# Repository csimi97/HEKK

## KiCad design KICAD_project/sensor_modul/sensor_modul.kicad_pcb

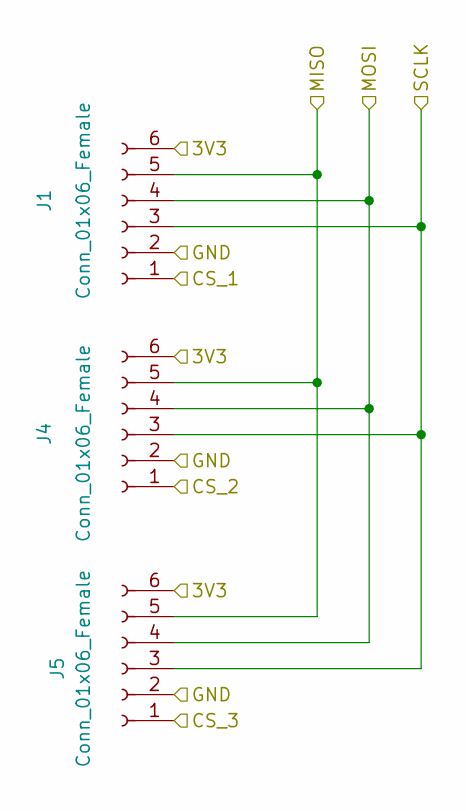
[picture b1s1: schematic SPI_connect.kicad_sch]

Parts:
J1, J4, J5: Conn_01x06_Female; PinHeader_1x06_P2.54mm_Vertical

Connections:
+3V3: J1.6, J4.6, J5.6; also elsewhere on the board
/EFR32/SPI_CLK: J1.3, J4.3, J5.3; also elsewhere on the board
/EFR32/SPI_CS1: J1.1; also elsewhere on the board
/EFR32/SPI_CS2: J4.1; also elsewhere on the board
/EFR32/SPI_CS3: J5.1; also elsewhere on the board
/EFR32/SPI_MISO: J1.5, J4.5, J5.5; also elsewhere on the board
/EFR32/SPI_MOSI: J1.4, J4.4, J5.4; also elsewhere on the board
GND: J1.2, J4.2, J5.2; also elsewhere on the board

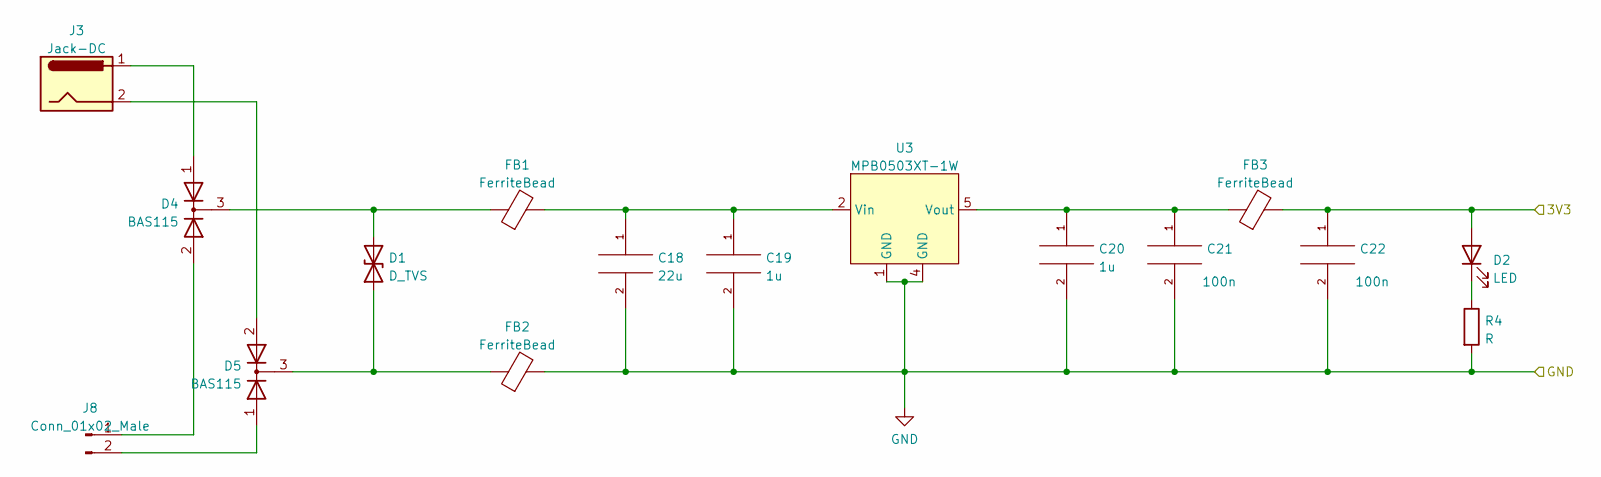
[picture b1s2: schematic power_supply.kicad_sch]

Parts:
C18: 22u; C_0805_2012Metric
C19, C20: 1u; C_0805_2012Metric
C21, C22: 100n; C_0805_2012Metric
D1: D_TVS; D_SMB
D2: LED; C_0805_2012Metric
D4, D5: BAS115; SOT-23
FB1, FB2, FB3: FerriteBead; L_0805_2012Metric
J3: Jack-DC; BarrelJack_CLIFF_FC681465S_SMT_Horizontal
J8: Conn_01x02_Male; PinHeader_1x02_P2.54mm_Vertical
R4: R; C_0805_2012Metric
U3: MPB0503XT-1W

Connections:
+3V3: C22.1, D2.2 (A), FB3.2; also elsewhere on the board
GND: C18.2, C19.2, C20.2, C21.2, C22.2, FB2.2, R4.2, U3.1 (GND), U3.4 (GND); also elsewhere on the board
unnamed: C18.1, C19.1, FB1.2, U3.2 (Vin)
unnamed: C20.1, C21.1, FB3.1, U3.5 (Vout)
unnamed: D1.1 (A1), D5.3 (K), FB2.1
unnamed: D1.2 (A2), D4.3 (K), FB1.1
unnamed: D2.1 (K), R4.1
unnamed: D4.1 (A), J3.1
unnamed: D4.2 (A), J8.1
unnamed: D5.1 (A), J8.2
unnamed: D5.2 (A), J3.2

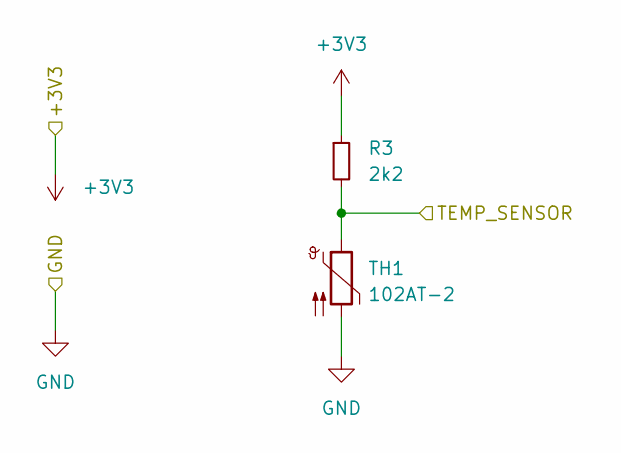
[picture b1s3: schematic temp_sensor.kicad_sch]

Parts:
R3: 2k2; R_0805_2012Metric
TH1: 102AT-2; PinHeader_1x02_P2.54mm_Vertical

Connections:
+3V3: R3.1; also elsewhere on the board
/EFR32/Temp_sense: R3.2, TH1.1; also elsewhere on the board
GND: TH1.2; also elsewhere on the board

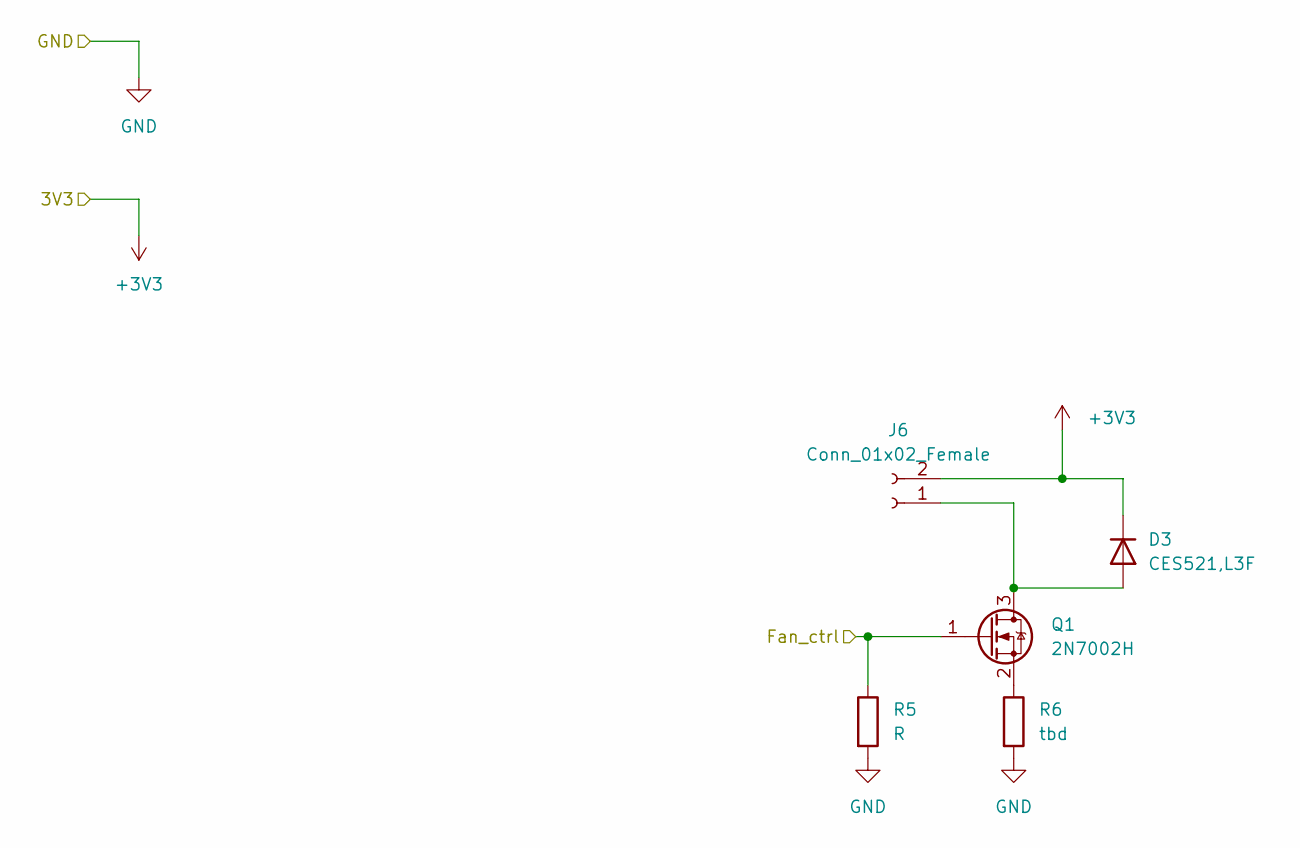
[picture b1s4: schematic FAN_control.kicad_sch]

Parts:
D3: CES521,L3F; D_SOD-523
J6: Conn_01x02_Female; PinHeader_1x02_P2.54mm_Vertical
Q1: 2N7002H; SOT-23
R5: R; R_0805_2012Metric
R6: tbd; R_0805_2012Metric

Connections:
+3V3: D3.1 (K), J6.2; also elsewhere on the board
/EFR32/FAN_ctrl: Q1.1 (G), R5.1; also elsewhere on the board
GND: R5.2, R6.2; also elsewhere on the board
unnamed: D3.2 (A), J6.1, Q1.3 (D)
unnamed: Q1.2 (S), R6.1

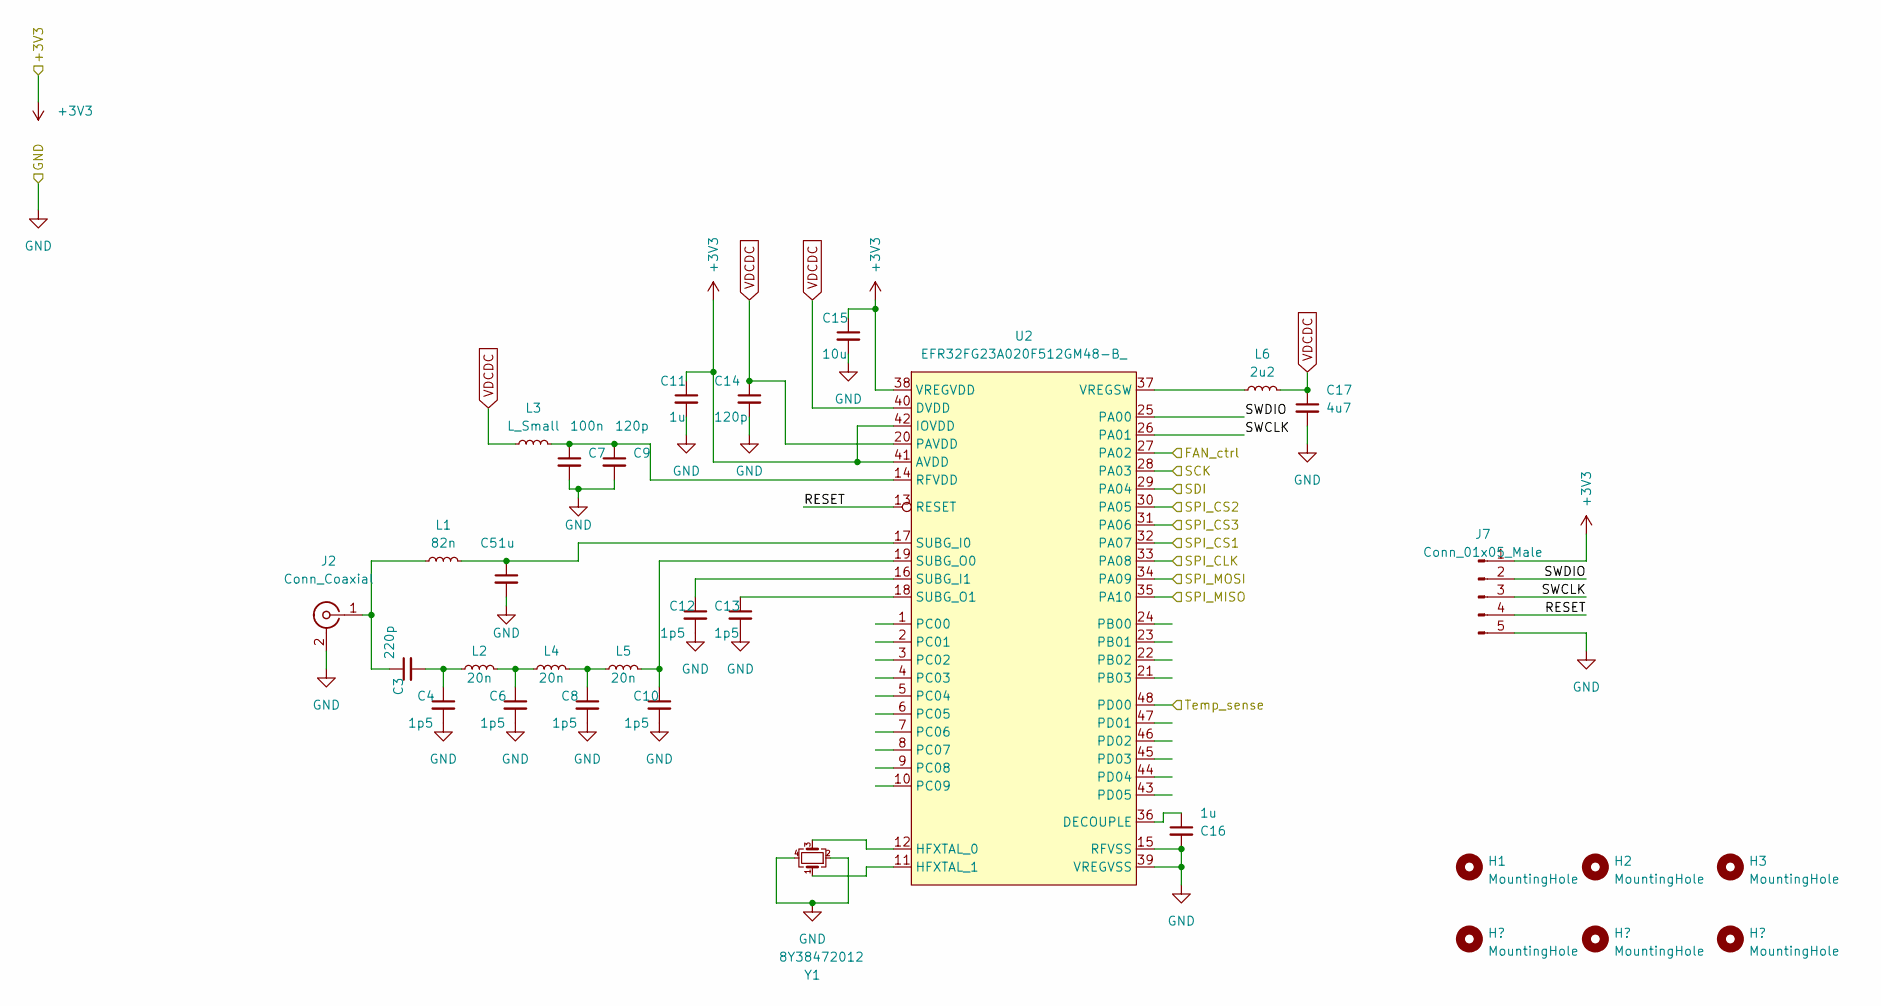
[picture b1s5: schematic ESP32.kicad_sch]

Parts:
C3: 220p; R_0402_1005Metric
C4, C6, C8, C10, C12, C13: 1p5; R_0402_1005Metric
C5: 1u; R_0402_1005Metric
C7: 100n; R_0402_1005Metric
C9, C14: 120p; R_0402_1005Metric
C11, C16: 1u; R_0805_2012Metric
C15: 10u; R_1206_3216Metric
C17: 4u7; R_0805_2012Metric
H1, H2, H3: MountingHole; MountingHole_2.2mm_M2
J2: Conn_Coaxial; SMA_Samtec_SMA-J-P-X-ST-EM1_EdgeMount
J7: Conn_01x05_Male; PinHeader_1x05_P2.54mm_Vertical
L1: 82n; R_0402_1005Metric
L2, L4, L5: 20n; R_0402_1005Metric
L3: L_Small; R_0402_1005Metric
L6: 2u2; R_0402_1005Metric
U2: EFR32FG23A020F512GM48-B_; EFR32FG23A020F512GM48-B
Y1: 8Y38472012; Oscillator_SMD_SeikoEpson_SG210-4Pin_2.5x2.0mm

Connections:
+3V3: C11.1, C15.1, J7.1, U2.38 (VREGVDD), U2.41 (AVDD), U2.42 (IOVDD); also elsewhere on the board
/Air_Quality_sensor/AQ_SENSOR_SCL: U2.28 (PA03); also elsewhere on the board
/Air_Quality_sensor/AQ_SENSOR_SDA: U2.29 (PA04); also elsewhere on the board
/EFR32/FAN_ctrl: U2.27 (PA02); also elsewhere on the board
/EFR32/RESET: J7.4, U2.13 (RESET)
/EFR32/SPI_CLK: U2.33 (PA08); also elsewhere on the board
/EFR32/SPI_CS1: U2.32 (PA07); also elsewhere on the board
/EFR32/SPI_CS2: U2.30 (PA05); also elsewhere on the board
/EFR32/SPI_CS3: U2.31 (PA06); also elsewhere on the board
/EFR32/SPI_MISO: U2.35 (PA10); also elsewhere on the board
/EFR32/SPI_MOSI: U2.34 (PA09); also elsewhere on the board
/EFR32/SWCLK: J7.3, U2.26 (PA01)
/EFR32/SWDIO: J7.2, U2.25 (PA00)
/EFR32/Temp_sense: U2.48 (PD00); also elsewhere on the board
GND: C4.2, C5.2, C6.2, C7.2, C8.2, C9.2, C10.2, C11.2, C12.2, C13.2, C14.2, C15.2, C16.2, C17.2, J2.2 (Ext), J7.5, U2.15 (RFVSS), U2.39 (VREGVSS), Y1.2, Y1.4; also elsewhere on the board
unnamed: C3.1, J2.1 (In), L1.1
unnamed: C3.2, C4.1, L2.1
unnamed: C5.1, L1.2, U2.17 (SUBG_I0)
unnamed: C6.1, L2.2, L4.1
unnamed: C7.1, C9.1, L3.2, U2.14 (RFVDD)
unnamed: C8.1, L4.2, L5.1
unnamed: C10.1, L5.2, U2.19 (SUBG_O0)
unnamed: C12.1, U2.16 (SUBG_I1)
unnamed: C13.1, U2.18 (SUBG_O1)
unnamed: C16.1, U2.36 (DECOUPLE)
unnamed: L6.1, U2.37 (VREGSW)
unnamed: U2.11 (HFXTAL_1), Y1.1
unnamed: U2.12 (HFXTAL_0), Y1.3
VDCDC: C14.1, C17.1, L3.1, L6.2, U2.20 (PAVDD), U2.40 (DVDD)

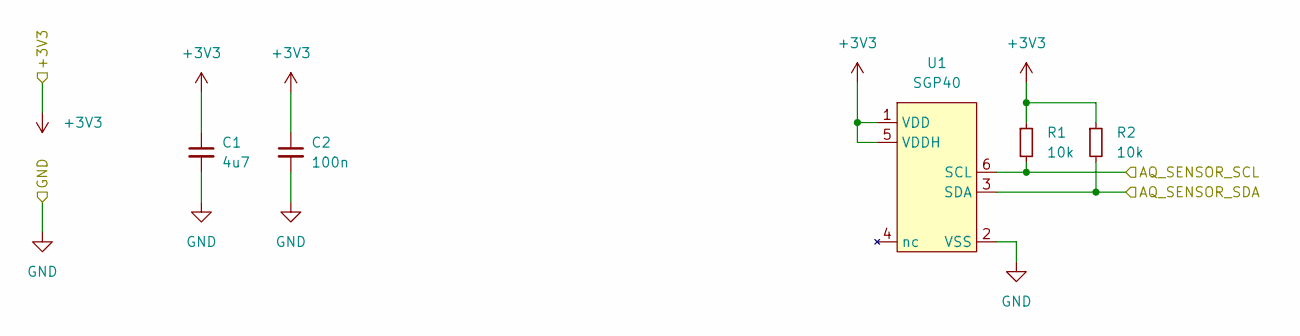
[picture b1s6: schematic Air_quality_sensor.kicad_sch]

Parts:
C1: 4u7; R_0805_2012Metric
C2: 100n; R_0805_2012Metric
R1, R2: 10k; R_0805_2012Metric
U1: SGP40

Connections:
+3V3: C1.1, C2.1, R1.1, R2.1, U1.1 (VDD), U1.5 (VDDH); also elsewhere on the board
/Air_Quality_sensor/AQ_SENSOR_SCL: R1.2, U1.6 (SCL); also elsewhere on the board
/Air_Quality_sensor/AQ_SENSOR_SDA: R2.2, U1.3 (SDA); also elsewhere on the board
GND: C1.2, C2.2, U1.2 (VSS), U1.7; also elsewhere on the board

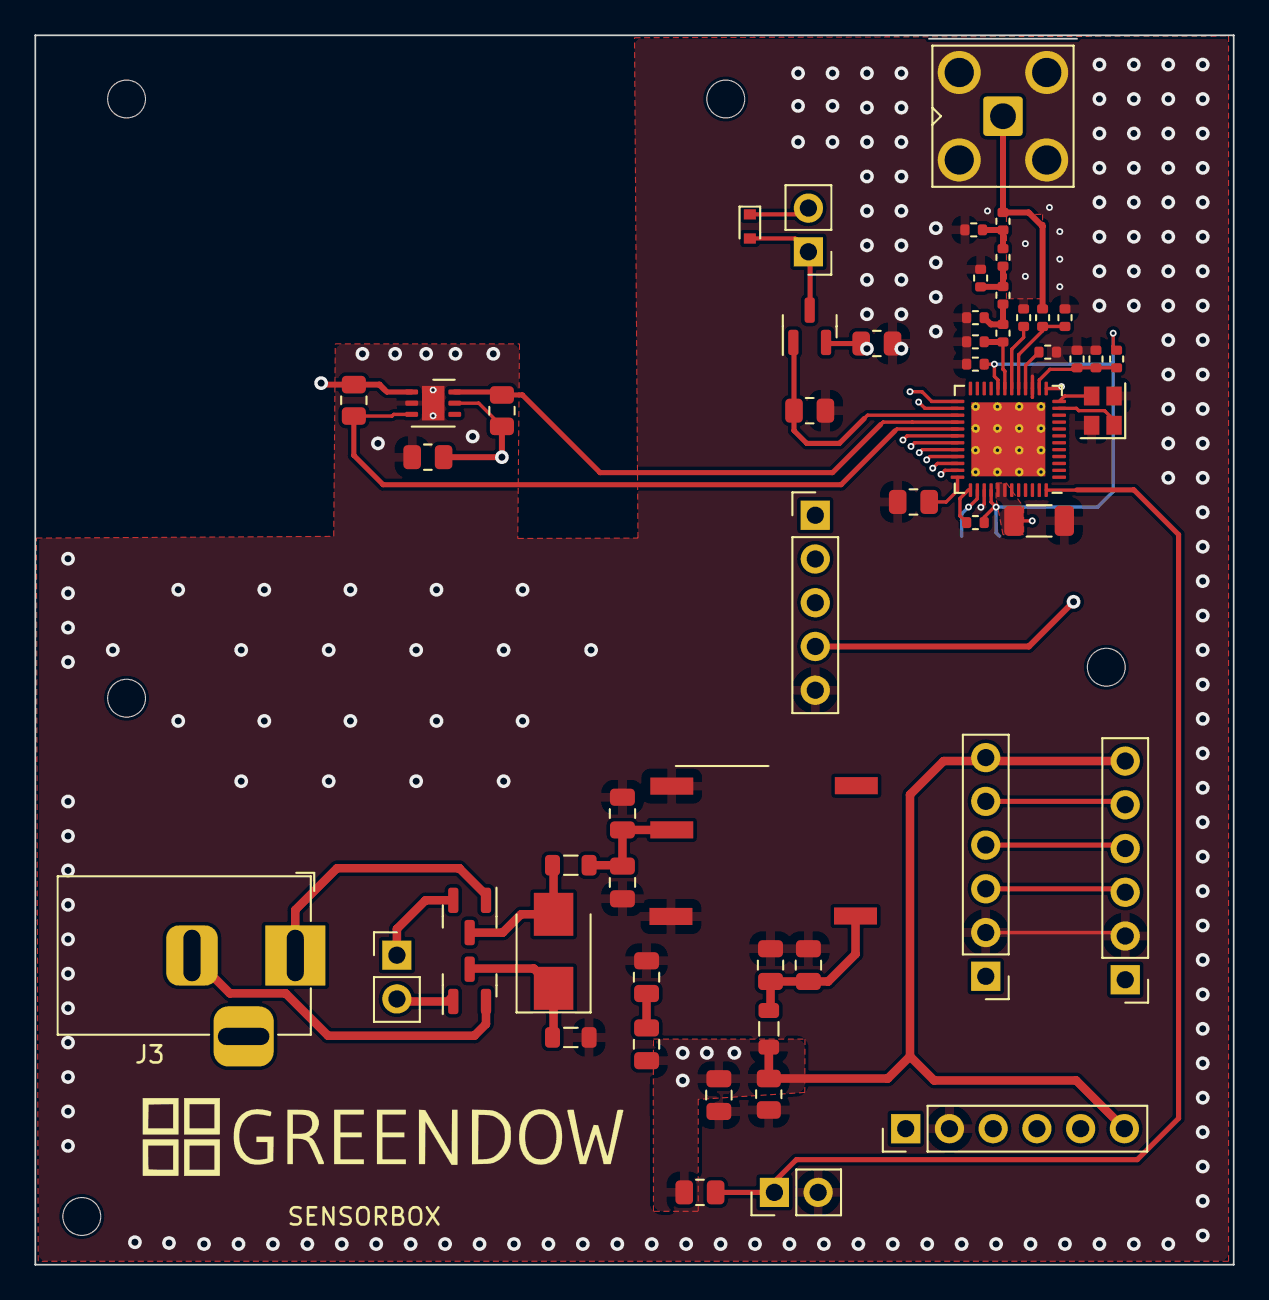
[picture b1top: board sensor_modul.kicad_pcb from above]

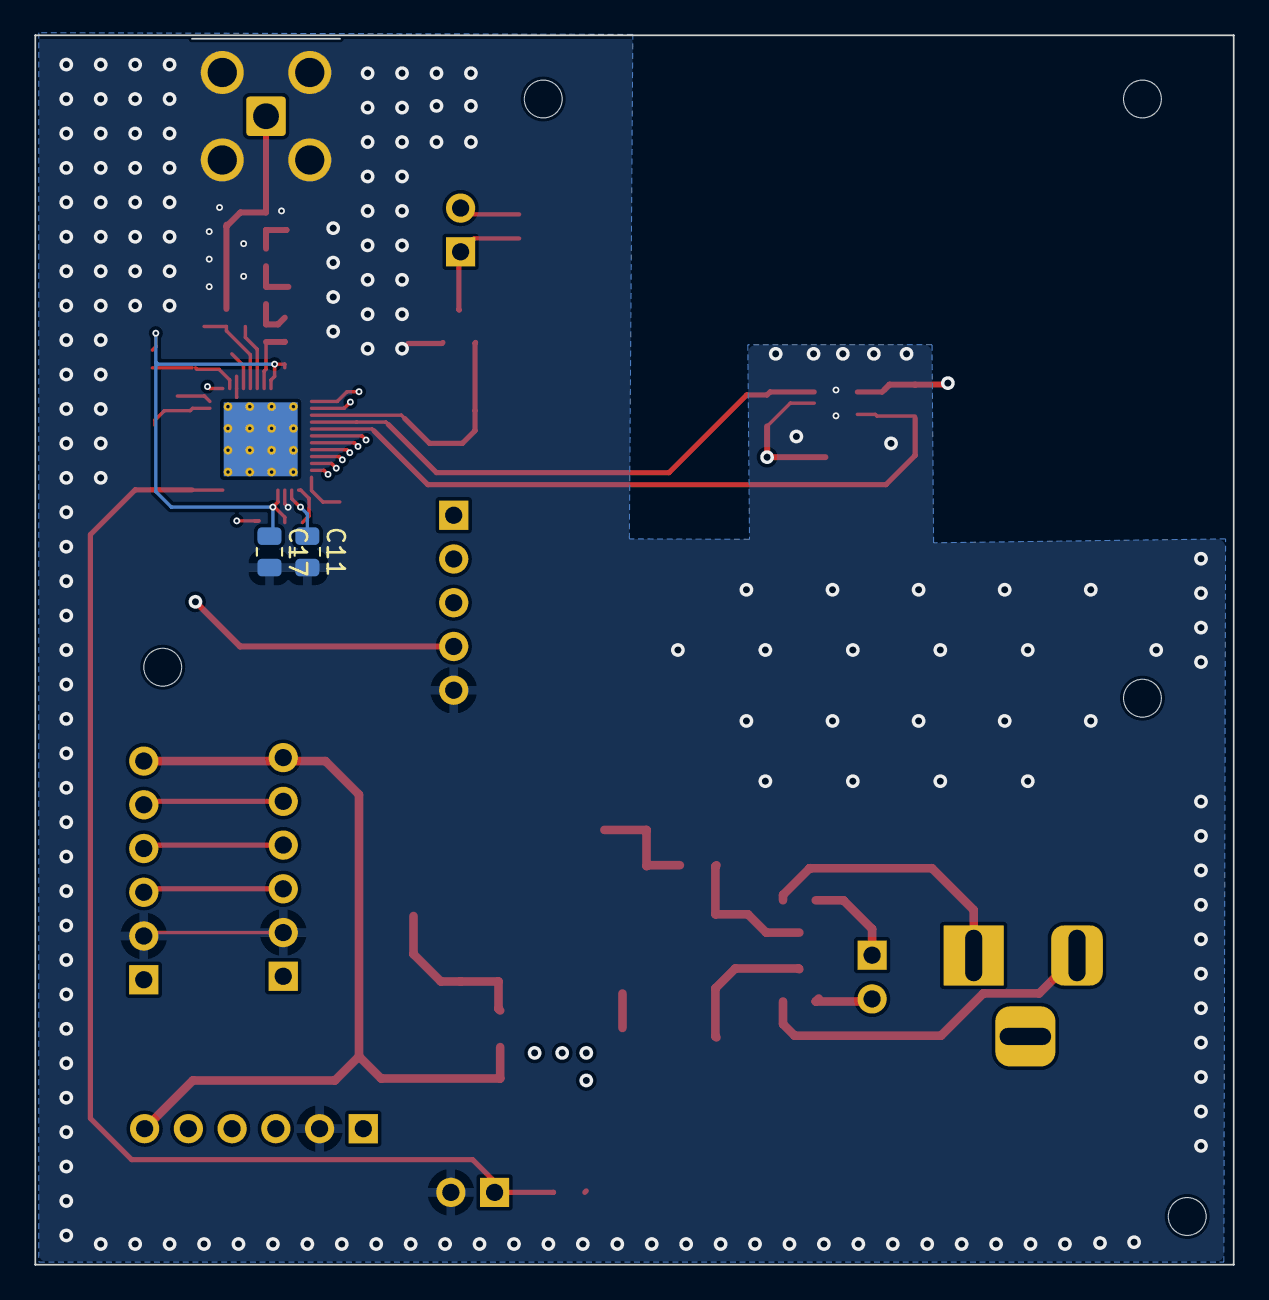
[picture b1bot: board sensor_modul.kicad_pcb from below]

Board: 4 copper layers, 69.6 x 71.4 mm, 61 parts (2 on the bottom side), 40 nets.

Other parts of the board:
H4, H6: MountingHole; MountingHole_2.2mm_M2

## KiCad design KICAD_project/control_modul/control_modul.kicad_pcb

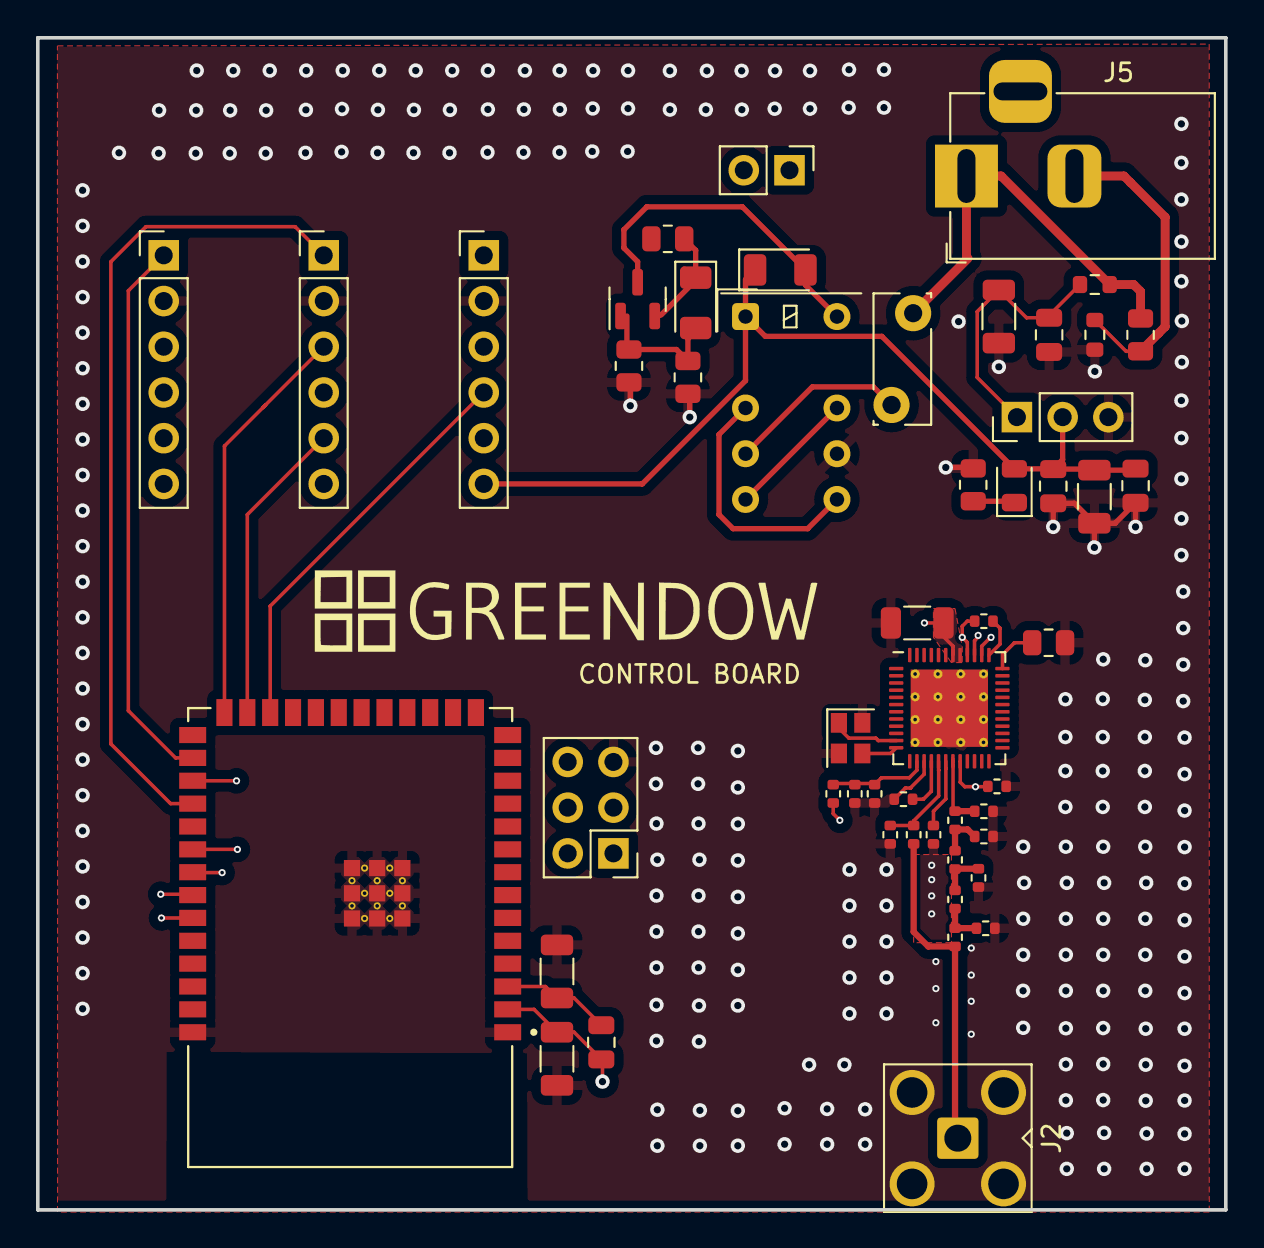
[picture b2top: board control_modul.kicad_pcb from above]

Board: 4 copper layers, 66.0 x 65.1 mm, 51 parts (0 on the bottom side), 37 nets.

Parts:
C1, C22: 22u; C_1206_3216Metric
C3: 220p; R_0402_1005Metric
C4, C6, C8, C10, C12, C13: 1p5; R_0402_1005Metric
C5: 1u; R_0402_1005Metric
C7: 100n; R_0402_1005Metric
C9, C14: 120p; R_0402_1005Metric
C15: 10u; R_1206_3216Metric
C16: 1u; R_0805_2012Metric
C18: 100n; C_1206_3216Metric
C19, C23: 1u; C_0805_2012Metric
C20: 33u; R_0805_2012Metric
C21: 10u; C_1206_3216Metric
C24: 100n; C_0805_2012Metric
D1, D2: 1N4148; D_1206_3216Metric
D3: D_TVS; R_0805_2012Metric
D4: LED; LED_0805_2012Metric
F1: Fuse; Fuse_Bourns_MF-RG300
FB2, FB3: FerriteBead; R_0603_1608Metric
J1, J3, J4: Conn_01x06_Female; PinHeader_1x06_P2.54mm_Vertical
J2: Conn_Coaxial; SMA_Amphenol_901-143_Horizontal
J5: Jack-DC; BarrelJack_Horizontal
J6: Conn_01x02_Female; PinHeader_1x02_P2.54mm_Vertical
J7: Conn_01x06_Female; PinHeader_2x03_P2.54mm_Vertical
K1: EC2-3NU; Relay_DPDT_Kemet_EC2
L1: 82n; R_0402_1005Metric
L2, L4, L5: 20n; R_0402_1005Metric
L3: L_Small; R_0402_1005Metric
L6: 2u2; R_0402_1005Metric
Q1: PN2222A; SOT-23
R1: 47k; R_0805_2012Metric
R2: 820k; R_0805_2012Metric
R3: 10k; C_0805_2012Metric
R4: R; R_0805_2012Metric
U1: ESP32; XCVR_ESP32-S3-WROOM-1-N16R2
U2: EFR32FG23A020F512GM48-B_; EFR32FG23A020F512GM48-B
U3: P78E05_1000; PinHeader_1x03_P2.54mm_Vertical
Y1: 8Y38472012; Oscillator_SMD_SeikoEpson_SG210-4Pin_2.5x2.0mm

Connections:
+3V3: C1.1, C15.1, C22.1, C23.1, C24.1, D2.1 (K), D4.2 (A), J1.6, J3.6, J4.6, J7.6, K1.1, R3.1, U1.2 (3V3), U2.38 (VREGVDD), U2.41 (AVDD), U2.42 (IOVDD), U3.2 (Vout)
+24V: D3.2 (A2), F1.1, FB3.1, J5.1
/ESP32/CS1: J1.1, U1.28 (IO35)
/ESP32/CS2: J3.1, U1.29 (IO36)
/ESP32/CS3: J4.1, U1.30 (IO37)
/ESP32/MISO: J1.5, J3.5, J4.5, U1.25 (IO48)
/ESP32/MOSI: J1.4, J3.4, J4.4, U1.24 (IO47)
/ESP32/SCLK: J1.3, J3.3, J4.3, U1.26 (IO45)
/ESP32/TCK: J7.2, U1.32 (IO39)
/ESP32/TDI: J7.4, U1.34 (IO41)
/ESP32/TDO: J7.3, U1.33 (IO40)
/ESP32/TMS: J7.1, U1.35 (IO42)
GND: C1.2, C4.2, C5.2, C6.2, C7.2, C8.2, C9.2, C10.2, C12.2, C13.2, C14.2, C15.2, C16.2, C18.1, C19.2, C20.2, C21.2, C22.2, C23.2, C24.2, FB2.2, J1.2, J2.2 (Ext), J3.2, J4.2, J7.5, K1.9, R2.1, R4.2, U1.1 (GND), U1.40 (GND), U1.41_1, U1.41_2, U1.41_3, U1.41_4, U1.41_5, U1.41_6, U1.41_7, U1.41_8, U1.41_9, U1.41_10, U1.41_11, U1.41_12, U1.41_13, U1.41_14, U1.41_15, U1.41_16, U1.41_17, U1.41_18, U1.41_19, U1.41_20, U1.41_21, U2.15 (RFVSS), U2.39 (VREGVSS), U2.49, U3.3 (GND), Y1.2, Y1.4
unnamed: C3.1, J2.1 (In), L1.1
unnamed: C3.2, C4.1, L2.1
unnamed: C5.1, L1.2, U2.17 (SUBG_I0)
unnamed: C6.1, L2.2, L4.1
unnamed: C7.1, C9.1, L3.2, U2.14 (RFVDD)
unnamed: C8.1, L4.2, L5.1
unnamed: C10.1, L5.2, U2.19 (SUBG_O0)
unnamed: C12.1, U2.16 (SUBG_I1)
unnamed: C13.1, U2.18 (SUBG_O1)
unnamed: C16.1, U2.36 (DECOUPLE)
unnamed: C18.2, R3.2, U1.3 (EN)
unnamed: C19.1, C21.1, FB3.2, U3.1 (Vin)
unnamed: C20.1, D1.2 (A), Q1.1 (E), R2.2
unnamed: D1.1 (K), Q1.2 (B), R1.2
unnamed: D2.2 (A), K1.12, Q1.3 (C)
unnamed: D3.1 (A1), FB2.1, J5.2
unnamed: D4.1 (K), R4.1
unnamed: F1.2, K1.4
unnamed: J6.2, K1.3, K1.8
unnamed: J6.1, K1.5, K1.10
unnamed: L6.1, U2.37 (VREGSW)
unnamed: U2.11 (HFXTAL_1), Y1.1
unnamed: U2.12 (HFXTAL_0), Y1.3
VDCDC: C14.1, L3.1, L6.2, U2.20 (PAVDD), U2.40 (DVDD)

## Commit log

2022-09-30 Create TESZT
2022-09-30 teszt
    as
2022-09-30 sdsdsdsdsds
2022-09-30 Boards_schematic_architecture
2022-10-01 control_board_ESP32_symbol_and_footprint
2022-10-01 Added EFR32 Sch and layout
    Added EFR32 Sch and layout
2022-10-01 delete_autosave
2022-10-01 Pull
    Pull
2022-10-01 ESP_to_libraries
2022-10-01 Fan_ctrl_sch
2022-10-01 autosave_del
2022-10-01 asdasd
2022-10-01 SPI_connect schematic
2022-10-01 Added EFR32 block
    Added EFR32 block
2022-10-01 power supply sensor module
2022-10-01 a
    a
2022-10-01 jolesz
2022-10-01 Basic docu
2022-10-01 sensor board
2022-10-01 fan ctrl
2022-10-01 Price calculations
2022-10-01 sensor_module_schematic_v1
2022-10-01 schematic_sensor_board
2022-10-01 asd
    asd
2022-10-01 sensor board pcb
2022-10-01 dolgok
2022-10-01 prezi haladás
2022-10-01 Töröltem a teszt_zsofi.txt-t
2022-10-01 pcb changes
2022-10-01 small changes
2022-10-01 before going home
2022-10-01 PCB_SENSOR_MODUL
2022-10-01 PCB UPDATE
2022-10-01 video 1.0
2022-10-01 pcb_done_sensor_box
2022-10-01 video 1.1
2022-10-01 sensor_pcb
2022-10-02 pcb_control_board
2022-10-02 PCB_last_update
2022-10-02 Upload and presentation done
2022-10-02 probably maybe final version
2022-10-02 final version 2 (ppt changes)
